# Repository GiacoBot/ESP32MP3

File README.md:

# **ESP32 MP3**

A self-built, portable MP3 player based on ESP32, combining a custom hardware design with an intuitive software interface. It reads music from an SD card, streams audio to any Bluetooth audio device, and is controlled via an OLED display and physical buttons.

## **Introduction**

This project evolved from a simple software experiment. The initial version was merely a proof-of-concept for Bluetooth audio streaming from an ESP32. Driven by the desire to create a complete and presentable product, I designed and built a custom dev board, developing an entire graphical and physical user interface from scratch.

The result is a functional and integrated device, demonstrating expertise in both hardware design (PCB design with KiCad) and complex firmware development (modular C++ architecture).

## **✨ Key Features**

#### **Hardware**

*   **Custom Dev Board (Rev 1.1)**: Development board entirely designed with KiCad to house all components compactly and functionally.
*   **0.96" OLED Display**: Monochrome screen (SSD1306 128x64) for a clear, low-power user interface.
*   **Physical Controls**: Interface navigation is managed by 5 physical buttons (Up, Down, Left, Right, Enter).
*   **MicroSD Card Storage**: A MicroSD card slot allows easy loading and playback of your music library.
*   **Power Management**: Power circuit with support for Li-Ion batteries and USB-C charging.

#### **Software**

*   **Bluetooth Audio Streaming (A2DP Source)**: Connects to Bluetooth headphones and speakers for high-quality wireless playback.
*   **Multi-screen User Interface**:
    *   **Bluetooth Device Selection**: Scans for nearby audio devices and manages the connection.
    *   **Track Selection**: Allows browsing the complete playlist of songs on the SD Card.
    *   **Now Playing**: Displays track information (if available), song title, artist, and a progress bar.
    *   **Volume Control**: Adjusts the playback volume directly from the interface.
*   **Advanced Playlist Management**: Automatically scans the SD card on startup to find all `.mp3` files.
*   **Intuitive User Input**: Supports short press, long press, and auto-repeat of buttons for smooth and fast navigation.
*   **Modular Firmware Architecture**: The code is organized into specialized "Managers" (Display, Input, Bluetooth, Player), making the system scalable, maintainable, and easy to debug.

## **⚙️ Hardware Details**

The development board was designed in KiCad to integrate the ESP32 with all necessary modules. The design is optimized for manual assembly and for use as a portable device.

*   **Design Software**: KiCad
*   **Main Processor**: ESP32-WROOM-32E module
*   **Display**: 0.96 inch (128x64) SSD1306 I2C/SPI OLED module
*   **Storage**: Standard MicroSD card reader
*   **Hardware Repository**: KiCad project files (schematics, PCB, and libraries) are available in the [`/Hardware/devboard Rev1.1`](/Hardware/devboard%20Rev1.1/) folder.

## **💻 Software Details**

The firmware is developed using the Arduino framework within PlatformIO, which simplifies dependency management and compilation.

*   **Framework**: Arduino / PlatformIO
*   **Key Libraries**:
    *   **[`U8g2`](https://github.com/olikraus/U8g2)**: Excellent library for managing monochrome displays.
    *   **[`arduino-audio-tools`](https://github.com/pschatzmann/arduino-audio-tools)**: For the audio decoding and processing pipeline.
    *   **[`ESP32-A2DP`](https://github.com/pschatzmann/ESP32-A2DP)**: For implementing the Bluetooth A2DP Source stack.
    *   **[`arduino-libhelix`](https://github.com/pschatzmann/arduino-libhelix)**: Provides the MP3 decoder based on Helix.
*   **Architecture**: The heart of the software is a state machine that manages navigation between different screens (`AppScreen`). The logic is divided into independent manager classes that communicate via an event system (`InputEvent`) and shared states, ensuring high cohesion and low coupling between modules.

## **🚀 Getting Started**

> [!NOTE]  
> If you want to try a simplified version of the project, you can try the alpha version, a proof of concept that only requires a breakout module for the micro SD and an ESP32 board. Follow the `README` in the alpha version for instructions.

#### **1. Hardware Prerequisites**

*   The assembled Dev Board.
*   A MicroSD card formatted as FAT32 and loaded with `.mp3` files. Is required for the files to have a sample rate of 44100 Hz, use the following `ffmpeg` command to convert files if needed:

    ```bash
    ffmpeg -i input.mp3 -ar 44100 output.mp3
    ```
*   A USB-C cable to upload the firmware.

#### **2. Software Setup**

The project is designed to be compiled with PlatformIO in Visual Studio Code.

1.  **Install VS Code and PlatformIO**: Follow the [official PlatformIO guide](https://platformio.org/install/ide?install=vscode).
2.  **Clone the Repository**:
    ```bash
    git clone https://github.com/GiacoBot/ESP32MP3.git
    cd ESP32MP3
    ```
3.  **Initialize Submodules**: The audio libraries are included as Git submodules.
    ```bash
    git submodule update --init --recursive
    ```

#### **3. Compile and Upload**

1.  **Open the Project**: In VS Code, open the project folder. Make sure to open the `Software` subfolder.
> [!IMPORTANT]  
> The PlatformIO project is located within the `Software` folder. When you open this project in VS Code, make sure you open the `Software` directory, not the root of the repository, to ensure PlatformIO can find all the necessary files.

1.  **Change Board settings**: Modify the `src/settings.h` file to match your hardware configuration if necessary (e.g., pin assignments).
2.  **Compile and Upload**: Use the PlatformIO commands (down arrow on the status bar) to build and upload the firmware to the board.

## **📸 Gallery**

Various screenshots of the user interface:

## **📜 License**

This project is released under the GPL-3.0 License. See the [LICENSE](LICENSE) file for more details.

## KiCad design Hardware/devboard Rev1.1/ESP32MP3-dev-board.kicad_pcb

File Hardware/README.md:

# Hardware

This folder contains the hardware design files for the project's custom development board.
Each hardware revision is organized in its own subfolder to keep designs clean, traceable, and easy to reference.

### Dev boards

* **Devboard Rev1.0** – First prototype of the dev board. Includes schematics, PCB layout, Gerber files, and BOM.
* **Devboard Rev1.1** – Updated revision addressing small issues found in Rev1.0. Recommended for new builds.

The development board is a semi-finished prototype, created to also validate the electrical design of the battery-charging circuitry and the buck-boost voltage regulation stage.
Its purpose is to verify the power system and provide a convenient and compact development board.

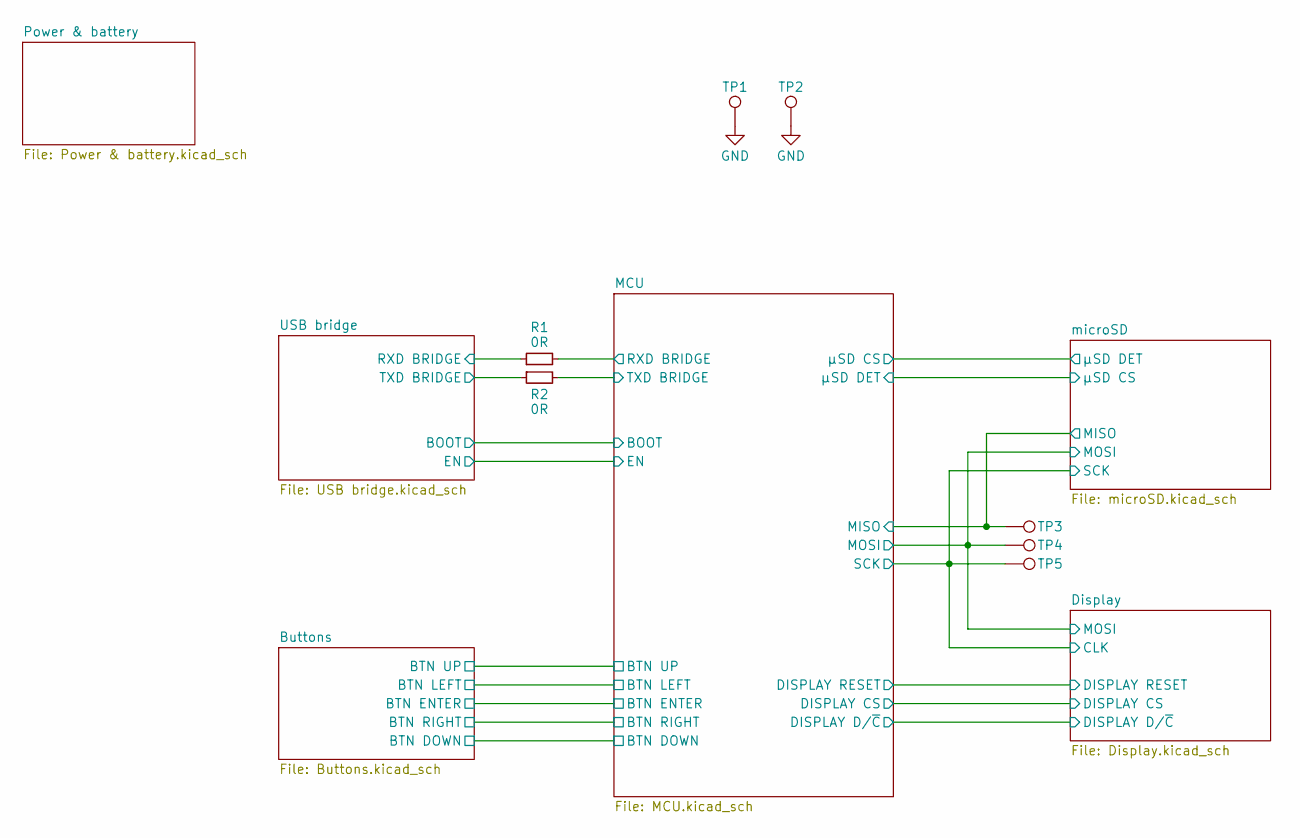
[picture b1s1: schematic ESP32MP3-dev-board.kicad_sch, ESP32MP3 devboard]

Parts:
R1, R2: 0R; R_0603_1608Metric_Pad0.98x0.95mm_HandSolder; Part Number YAGEO RC0603JR-070RL
TP1, TP2: GND; TestPoint_Pad_1.0x1.0mm
TP3: MISO; TestPoint_Pad_D1.0mm
TP4: MOSI; TestPoint_Pad_D1.0mm
TP5: SCK; TestPoint_Pad_D1.0mm

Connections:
/Display/CLK: TP5.1; also elsewhere on the board
/Display/MOSI: TP4.1; also elsewhere on the board
/MCU/MISO: TP3.1; also elsewhere on the board
/MCU/RXD BRIDGE: R1.2; also elsewhere on the board
/MCU/TXD BRIDGE: R2.2; also elsewhere on the board
/USB bridge/RXD BRIDGE: R1.1; also elsewhere on the board
/USB bridge/TXD BRIDGE: R2.1; also elsewhere on the board
GND: TP1.1, TP2.1; also elsewhere on the board

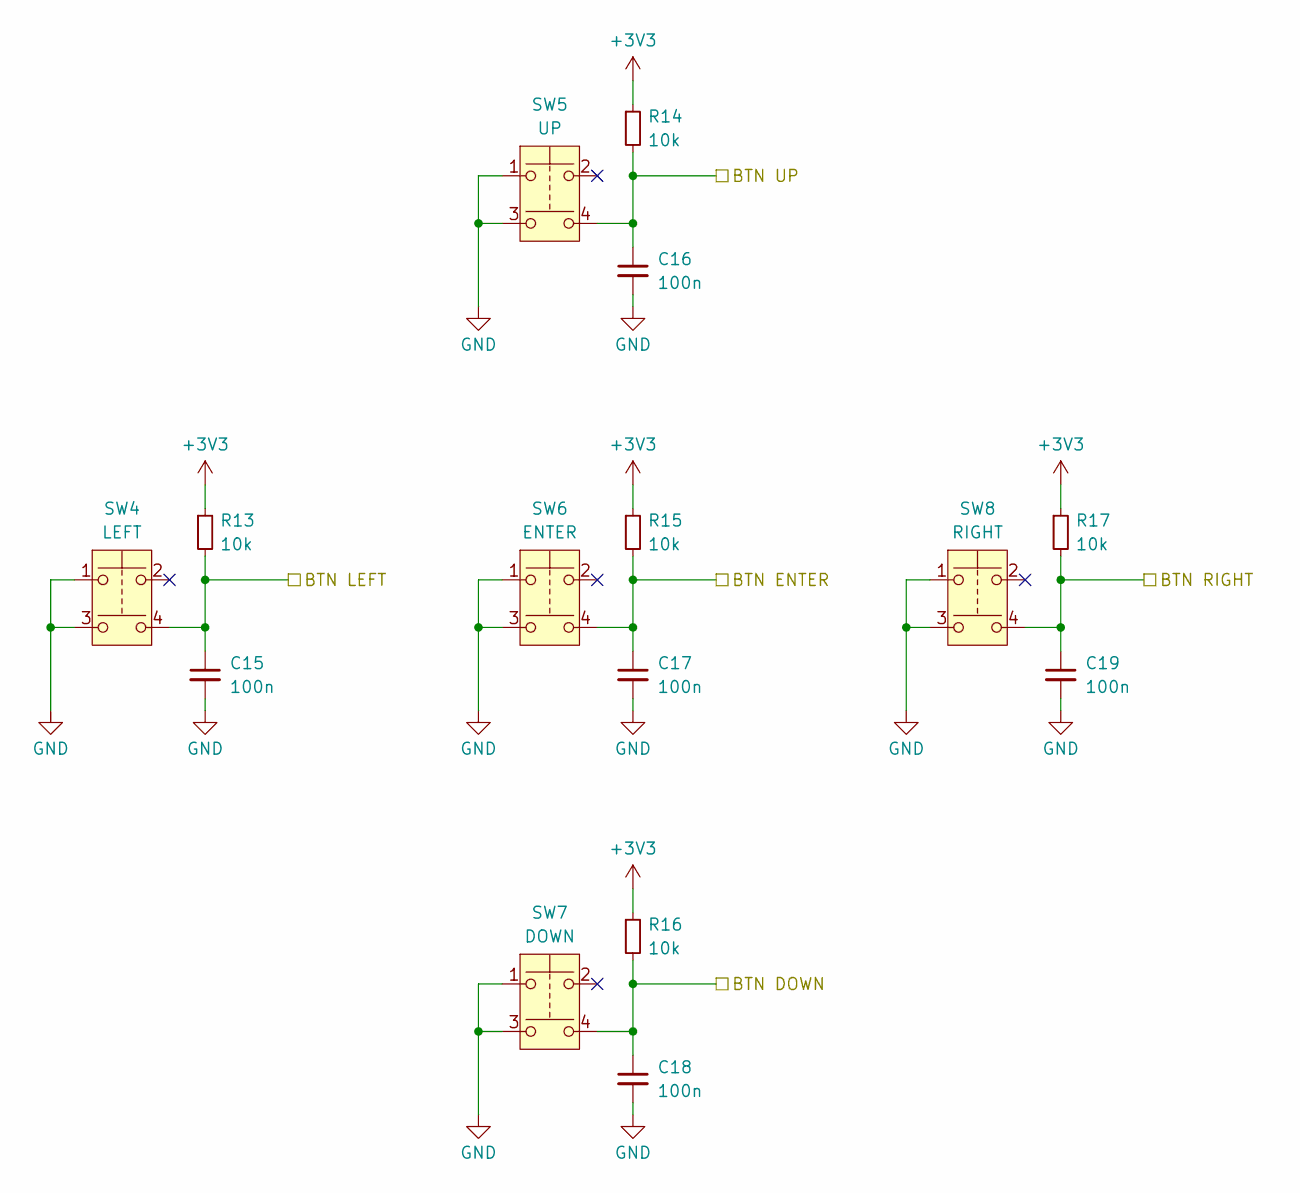
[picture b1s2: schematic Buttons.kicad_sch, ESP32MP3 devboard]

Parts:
C15, C16, C17, C18, C19: 100n; C_0603_1608Metric; Part Number YAGEO CC0603KRX7R9BB104
R13, R14, R15, R16, R17: 10k; R_0603_1608Metric_Pad0.98x0.95mm_HandSolder; Part Number YAGEO RC0603FR-0710KL
SW4: LEFT; PTS526SM15SMTR2LFS; Part Number C&K PTS526SK15SMTR2LFS
SW5: UP; PTS526SM15SMTR2LFS; Part Number C&K PTS526SK15SMTR2LFS
SW6: ENTER; PTS526SM15SMTR2LFS; Part Number C&K PTS526SK15SMTR2LFS
SW7: DOWN; PTS526SM15SMTR2LFS; Part Number C&K PTS526SK15SMTR2LFS
SW8: RIGHT; PTS526SM15SMTR2LFS; Part Number C&K PTS526SK15SMTR2LFS

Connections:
+3V3: R13.1, R14.1, R15.1, R16.1, R17.1; also elsewhere on the board
/Buttons/BTN DOWN: C18.1, R16.2, SW7.4; also elsewhere on the board
/Buttons/BTN ENTER: C17.1, R15.2, SW6.4; also elsewhere on the board
/Buttons/BTN LEFT: C15.1, R13.2, SW4.4; also elsewhere on the board
/Buttons/BTN RIGHT: C19.1, R17.2, SW8.4; also elsewhere on the board
/Buttons/BTN UP: C16.1, R14.2, SW5.4; also elsewhere on the board
GND: C15.2, C16.2, C17.2, C18.2, C19.2, SW4.1, SW4.3, SW5.1, SW5.3, SW6.1, SW6.3, SW7.1, SW7.3, SW8.1, SW8.3; also elsewhere on the board

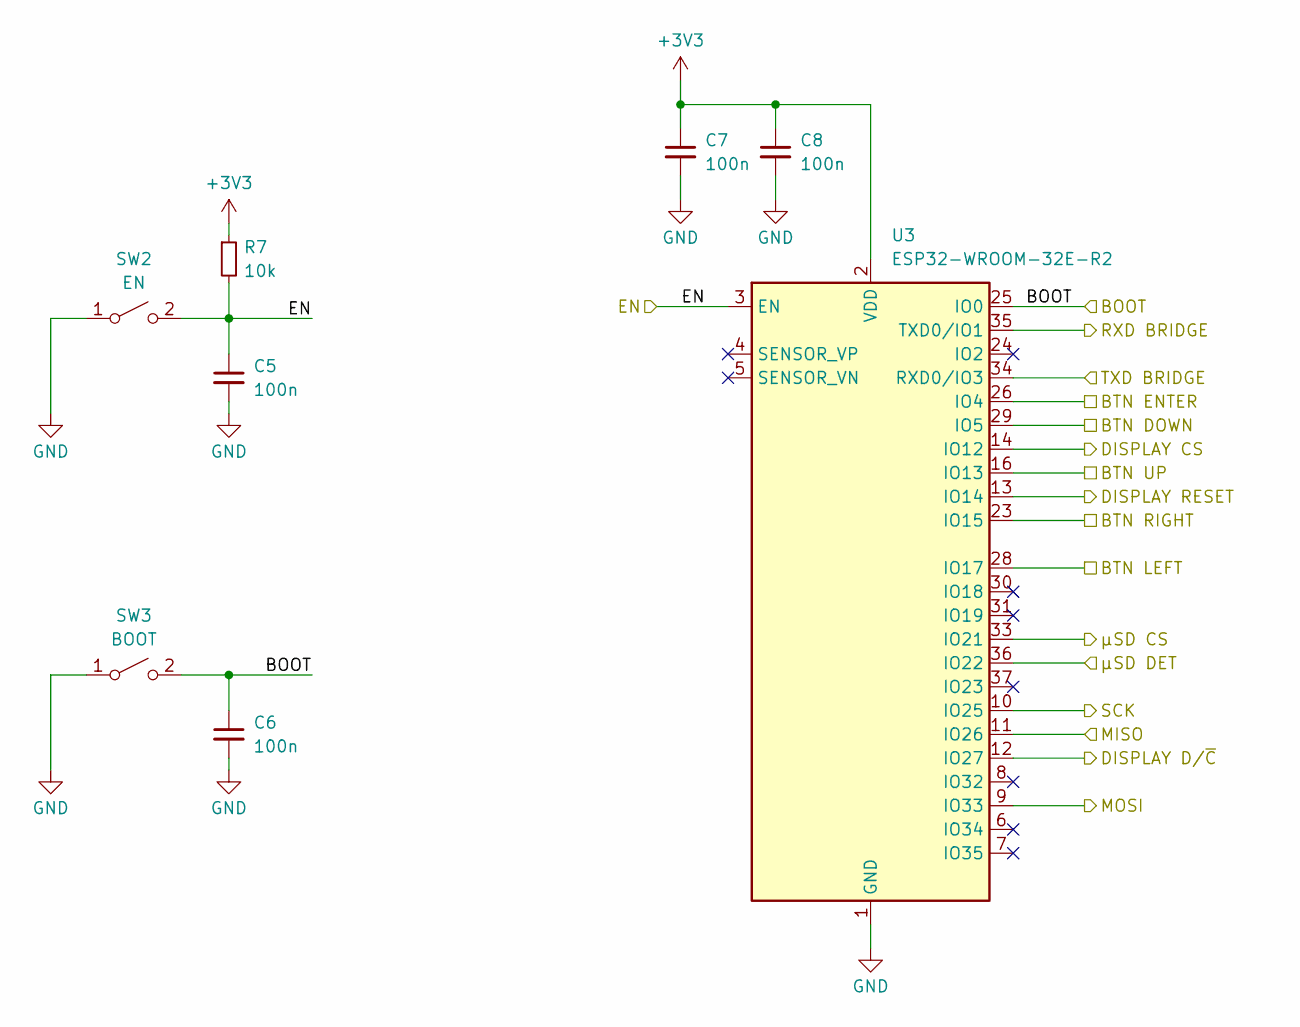
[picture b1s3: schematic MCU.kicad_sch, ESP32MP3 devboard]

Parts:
C5, C6, C7, C8: 100n; C_0603_1608Metric; Part Number YAGEO CC0603KRX7R9BB104
R7: 10k; R_0603_1608Metric_Pad0.98x0.95mm_HandSolder; Part Number YAGEO RC0603FR-0710KL
SW2: EN; SW_TS-1088-AR02016; Part Number XUNPU TS-1088-AR02016
SW3: BOOT; SW_TS-1088-AR02016; Part Number XUNPU TS-1088-AR02016
U3: ESP32-WROOM-32E-R2; ESP32-WROOM-32D; Part Number ESPRESSIF ESP32-WROOM-32E-N8R2

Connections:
+3V3: C7.1, C8.1, R7.1, U3.2 (VDD); also elsewhere on the board
/Buttons/BTN DOWN: U3.29 (IO5); also elsewhere on the board
/Buttons/BTN ENTER: U3.26 (IO4); also elsewhere on the board
/Buttons/BTN LEFT: U3.28 (IO17); also elsewhere on the board
/Buttons/BTN RIGHT: U3.23 (IO15); also elsewhere on the board
/Buttons/BTN UP: U3.16 (IO13); also elsewhere on the board
/Display/CLK: U3.10 (IO25); also elsewhere on the board
/Display/DISPLAY CS: U3.14 (IO12); also elsewhere on the board
/Display/DISPLAY D/~C: U3.12 (IO27); also elsewhere on the board
/Display/DISPLAY RESET: U3.13 (IO14); also elsewhere on the board
/Display/MOSI: U3.9 (IO33); also elsewhere on the board
/MCU/BOOT: C6.1, SW3.2 (B), U3.25 (IO0); also elsewhere on the board
/MCU/EN: C5.1, R7.2, SW2.2 (B), U3.3 (EN); also elsewhere on the board
/MCU/MISO: U3.11 (IO26); also elsewhere on the board
/MCU/RXD BRIDGE: U3.35 (TXD0/IO1); also elsewhere on the board
/MCU/TXD BRIDGE: U3.34 (RXD0/IO3); also elsewhere on the board
/MCU/µSD CS: U3.33 (IO21); also elsewhere on the board
/MCU/µSD DET: U3.36 (IO22); also elsewhere on the board
GND: C5.2, C6.2, C7.2, C8.2, SW2.1 (A), SW3.1 (A), U3.1 (GND), U3.15 (GND), U3.38 (GND), U3.39 (GND); also elsewhere on the board

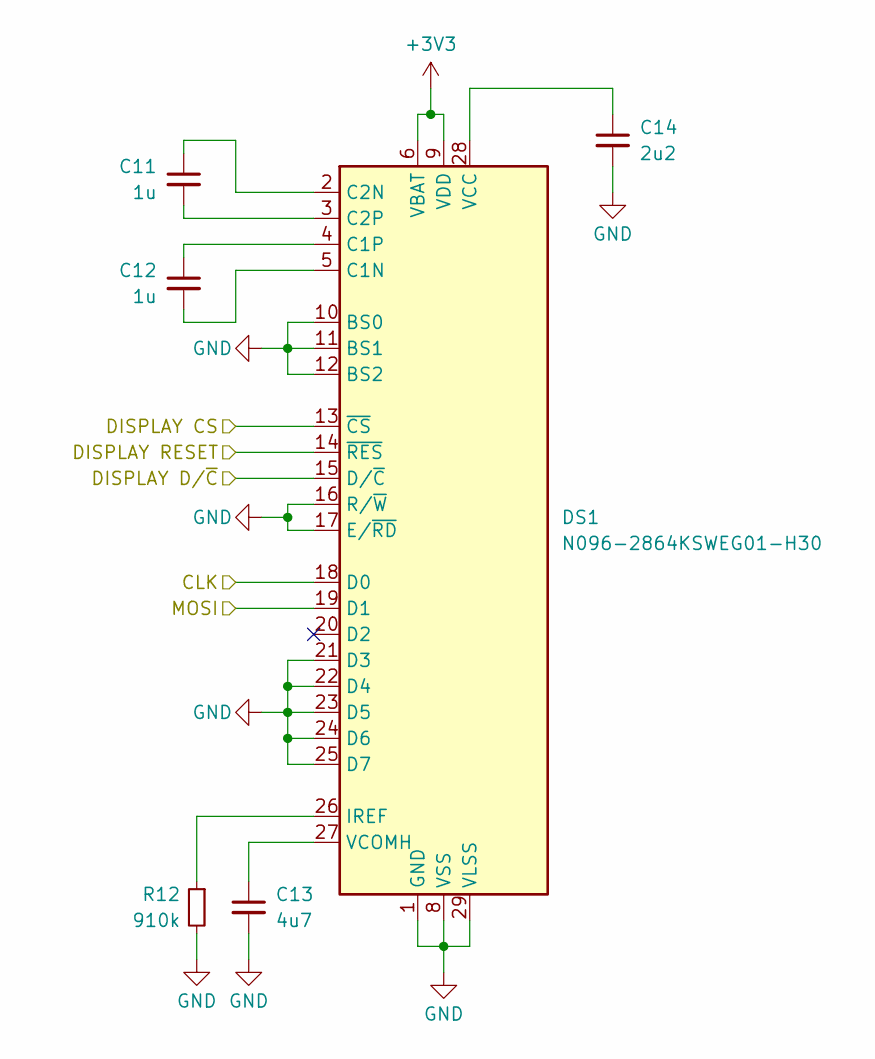
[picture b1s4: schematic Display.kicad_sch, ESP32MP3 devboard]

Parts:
C11, C12: 1u; C_0603_1608Metric; Part Number Samsung Electro-Mechanics CL10B105KA8NN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
C13: 4u7; C_0603_1608Metric; Part Number Samsung Electro-Mechanics CL10A475KA8NQ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
C14: 2u2; C_0603_1608Metric; Part Number muRata GRM188Z71E225KE43D
DS1: N096-2864KSWEG01-H30; Part Number Wisevision N096-2864KSWEG01-H30
R12: 910k; R_0603_1608Metric_Pad0.98x0.95mm_HandSolder; Part Number YAGEO RC0603FR-07910KL

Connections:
+3V3: DS1.6 (VBAT), DS1.9 (VDD); also elsewhere on the board
/Display/CLK: DS1.18 (D0); also elsewhere on the board
/Display/DISPLAY CS: DS1.13 (~CS); also elsewhere on the board
/Display/DISPLAY D/~C: DS1.15 (D/~C); also elsewhere on the board
/Display/DISPLAY RESET: DS1.14 (~RES); also elsewhere on the board
/Display/MOSI: DS1.19 (D1); also elsewhere on the board
GND: C13.2, C14.2, DS1.1 (GND), DS1.8 (VSS), DS1.10 (BS0), DS1.11 (BS1), DS1.12 (BS2), DS1.16 (R/~W), DS1.17 (E/~RD), DS1.21 (D3), DS1.22 (D4), DS1.23 (D5), DS1.24 (D6), DS1.25 (D7), DS1.29 (VLSS), DS1.30 (GND), R12.2; also elsewhere on the board
unnamed: C12.2, DS1.5 (C1N)
unnamed: C12.1, DS1.4 (C1P)
unnamed: C11.1, DS1.2 (C2N)
unnamed: C11.2, DS1.3 (C2P)
unnamed: DS1.26 (IREF), R12.1
unnamed: C14.1, DS1.28 (VCC)
unnamed: C13.1, DS1.27 (VCOMH)

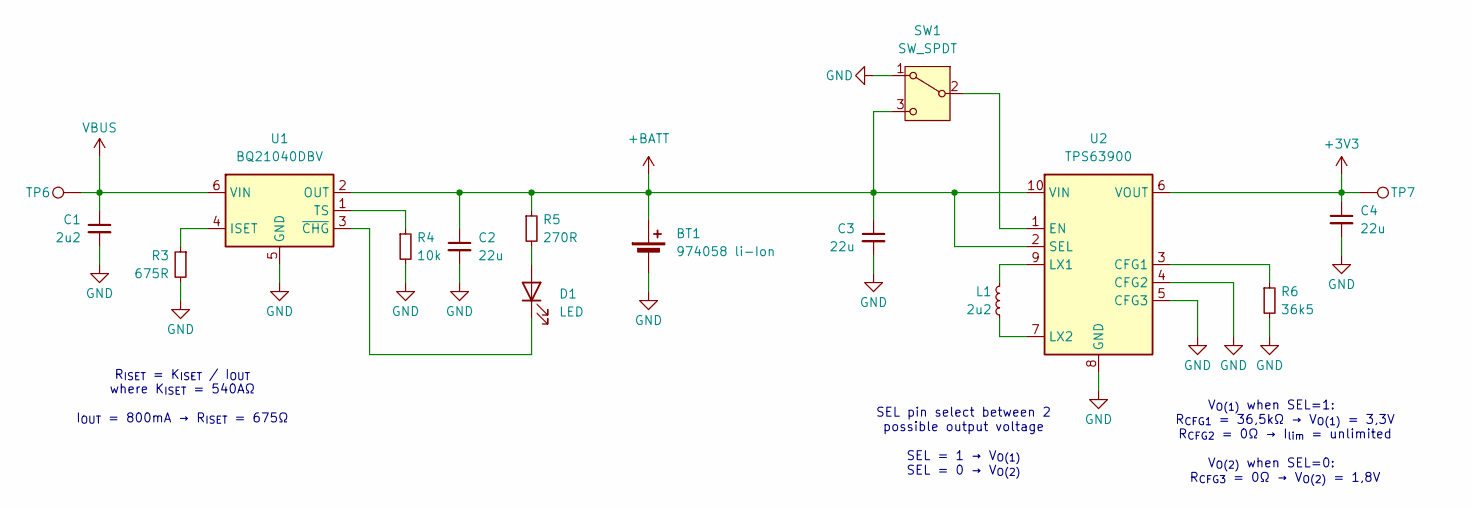
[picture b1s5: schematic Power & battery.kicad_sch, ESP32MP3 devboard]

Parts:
BT1: 974058 li-Ion; JST_PH_S2B-PH-SM4-TB_1x02-1MP_P2.00mm_Horizontal; Part Number JST S2B-PH-SM4-TB(LF)(SN)
C1: 2u2; C_0603_1608Metric; Part Number muRata GRM188Z71E225KE43D
C2, C3, C4: 22u; C_0603_1608Metric; Part Number Samsung Electro-Mechanics CL10A226MP8NU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
D1: LED; LED_0603_1608Metric; Part Number EVERLIGHT 19-219/GHC-YR2T1B5Y/3T
L1: 2u2; L_1008_2520Metric; Part Number ZE ZEMS252012-2R2M
R3: 675R; R_0603_1608Metric_Pad0.98x0.95mm_HandSolder; Part Number YAGEO RC0603FR-07680RL
R4: 10k; R_0603_1608Metric_Pad0.98x0.95mm_HandSolder; Part Number YAGEO RC0603FR-0710KL
R5: 270R; R_0603_1608Metric_Pad0.98x0.95mm_HandSolder; Part Number YAGEO RC0603FR-07270RL
R6: 36k5; R_0603_1608Metric_Pad0.98x0.95mm_HandSolder; Part Number YAGEO RT0603BRE0736K5L
SW1: SW_SPDT; MK-12C02-G015; Part Number G-Switch MK-12C02-G015
TP6: 5V; TestPoint_Pad_D1.0mm
TP7: 3V3; TestPoint_Pad_D1.0mm
U1: BQ21040DBV; SOT-23-6; Part Number TI BQ21040DBVR
U2: TPS63900; WSON-10-1EP_2.5x2.5mm_P0.5mm_EP1.2x2mm_ThermalVias; Part Number TI TPS63900DSKR

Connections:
+3V3: C4.1, TP7.1, U2.6 (VOUT); also elsewhere on the board
+BATT: BT1.2 (+), C2.1, C3.1, R5.1, SW1.3 (C), U1.2 (OUT), U2.2 (SEL), U2.10 (VIN)
GND: BT1.1 (-), C1.2, C2.2, C3.2, C4.2, R3.2, R4.2, R6.2, SW1.1 (A), U1.5 (GND), U2.4 (CFG2), U2.5 (CFG3), U2.8 (GND), U2.11 (GND); also elsewhere on the board
unnamed: D1.2 (A), R5.2
unnamed: D1.1 (K), U1.3 (~CHG)
unnamed: SW1.2 (B), U2.1 (EN)
unnamed: R3.1, U1.4 (ISET)
unnamed: R4.1, U1.1 (TS)
unnamed: R6.1, U2.3 (CFG1)
unnamed: L1.1, U2.9 (LX1)
unnamed: L1.2, U2.7 (LX2)
VBUS: C1.1, TP6.1, U1.6 (VIN); also elsewhere on the board

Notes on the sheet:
R_{ISET} = K_{ISET} / I_{OUT} where K_{ISET} = 540AΩ I_{OUT} = 800mA → R_{ISET} = 675Ω
SEL pin select between 2 possible output voltage SEL = 1 → V_{O(1)} SEL = 0 → V_{O(2)}
V_{O(1)} when SEL=1: R_{CFG1} = 36,5kΩ → V_{O(1)} = 3,3V R_{CFG2} = 0Ω → I_{lim} = unlimited V_{O(2)} when SEL=0: R_{CFG3} = 0Ω → V_{O(2)} = 1,8V

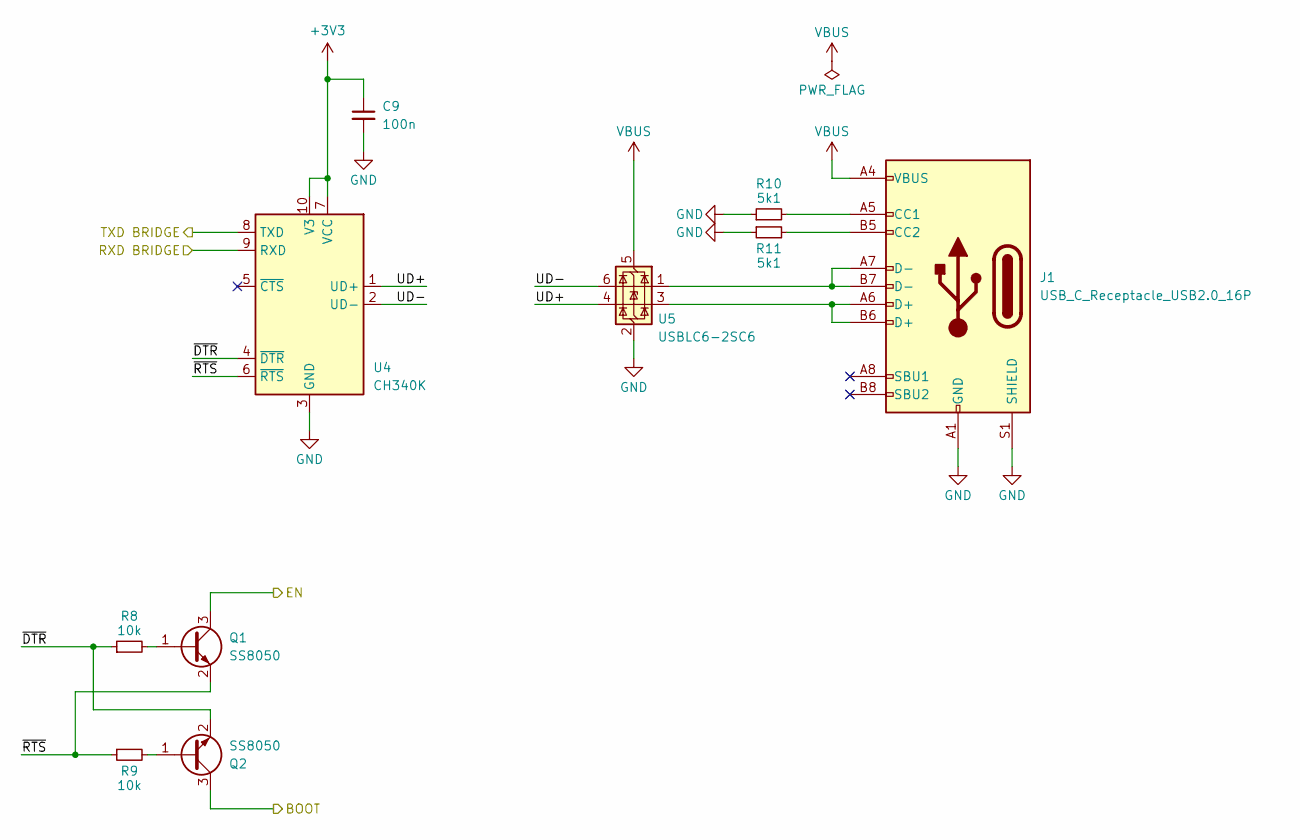
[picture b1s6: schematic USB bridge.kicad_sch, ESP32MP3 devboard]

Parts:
C9: 100n; C_0603_1608Metric; Part Number YAGEO CC0603KRX7R9BB104
J1: USB_C_Receptacle_USB2.0_16P; USB_C_Receptacle_GCT_USB4110; Part Number DEALON USB-TYPE-C-020
Q1, Q2: SS8050; SOT-23-3; Part Number Chao He SS8050
R8, R9: 10k; R_0603_1608Metric_Pad0.98x0.95mm_HandSolder; Part Number YAGEO RC0603FR-0710KL
R10, R11: 5k1; R_0603_1608Metric_Pad0.98x0.95mm_HandSolder; Part Number YAGEO RC0603FR-075K1L
U4: CH340K; SSOP-10-1EP_3.9x4.9mm_P1mm_EP2.1x3.3mm; Part Number WCH CH340K
U5: USBLC6-2SC6; SOT-23-6; Part Number TECH PUBLIC USBLC6-2SC6

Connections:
+3V3: C9.1, U4.7 (VCC), U4.10 (V3); also elsewhere on the board
/MCU/BOOT: Q2.3 (C); also elsewhere on the board
/MCU/EN: Q1.3 (C); also elsewhere on the board
/USB bridge/RXD BRIDGE: U4.9 (RXD); also elsewhere on the board
/USB bridge/TXD BRIDGE: U4.8 (TXD); also elsewhere on the board
/USB bridge/UD+: U4.1 (UD+), U5.4 (I/O2)
/USB bridge/UD-: U4.2 (UD-), U5.6 (I/O1)
/USB bridge/~DTR: Q2.2 (E), R8.1, U4.4 (~DTR)
/USB bridge/~RTS: Q1.2 (E), R9.1, U4.6 (~RTS)
GND: C9.2, J1.A1 (GND), J1.A12 (GND), J1.B1 (GND), J1.B12 (GND), J1.S1 (SHIELD), R10.1, R11.1, U4.3 (GND), U4.11 (GND), U5.2 (GND); also elsewhere on the board
unnamed: J1.A5 (CC1), R10.2
unnamed: J1.B5 (CC2), R11.2
unnamed: J1.A6 (D+), J1.B6 (D+), U5.3 (I/O2)
unnamed: J1.A7 (D-), J1.B7 (D-), U5.1 (I/O1)
unnamed: Q1.1 (B), R8.2
unnamed: Q2.1 (B), R9.2
VBUS: J1.A4 (VBUS), J1.A9 (VBUS), J1.B4 (VBUS), J1.B9 (VBUS), U5.5 (VBUS); also elsewhere on the board

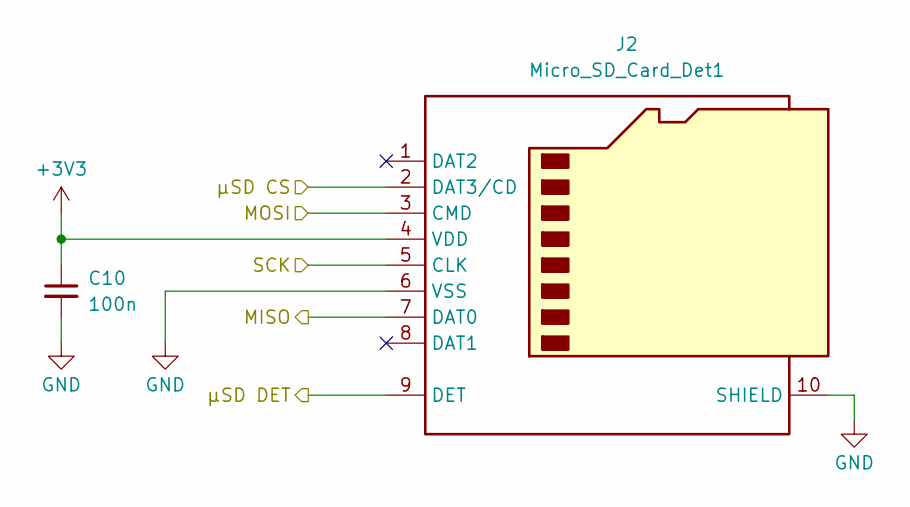
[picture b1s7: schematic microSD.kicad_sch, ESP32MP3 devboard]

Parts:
C10: 100n; C_0603_1608Metric; Part Number YAGEO CC0603KRX7R9BB104
J2: Micro_SD_Card_Det1; TF PUSH; Part Number SHOU HAN TF PUSH

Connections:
+3V3: C10.1, J2.4 (VDD); also elsewhere on the board
/Display/CLK: J2.5 (CLK); also elsewhere on the board
/Display/MOSI: J2.3 (CMD); also elsewhere on the board
/MCU/MISO: J2.7 (DAT0); also elsewhere on the board
/MCU/µSD CS: J2.9 (DET); also elsewhere on the board
/MCU/µSD DET: J2.2 (DAT3/CD); also elsewhere on the board
GND: C10.2, J2.6 (VSS), J2.10 (SHIELD); also elsewhere on the board

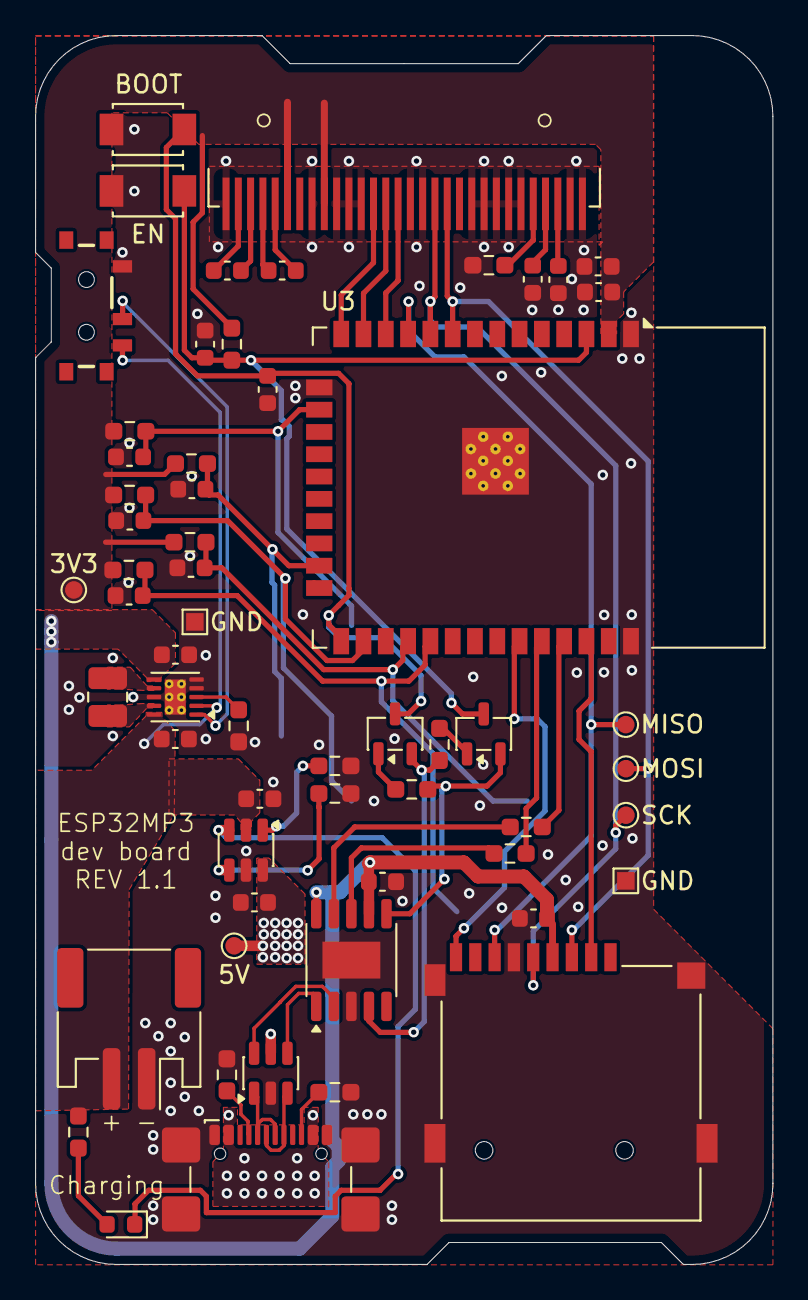
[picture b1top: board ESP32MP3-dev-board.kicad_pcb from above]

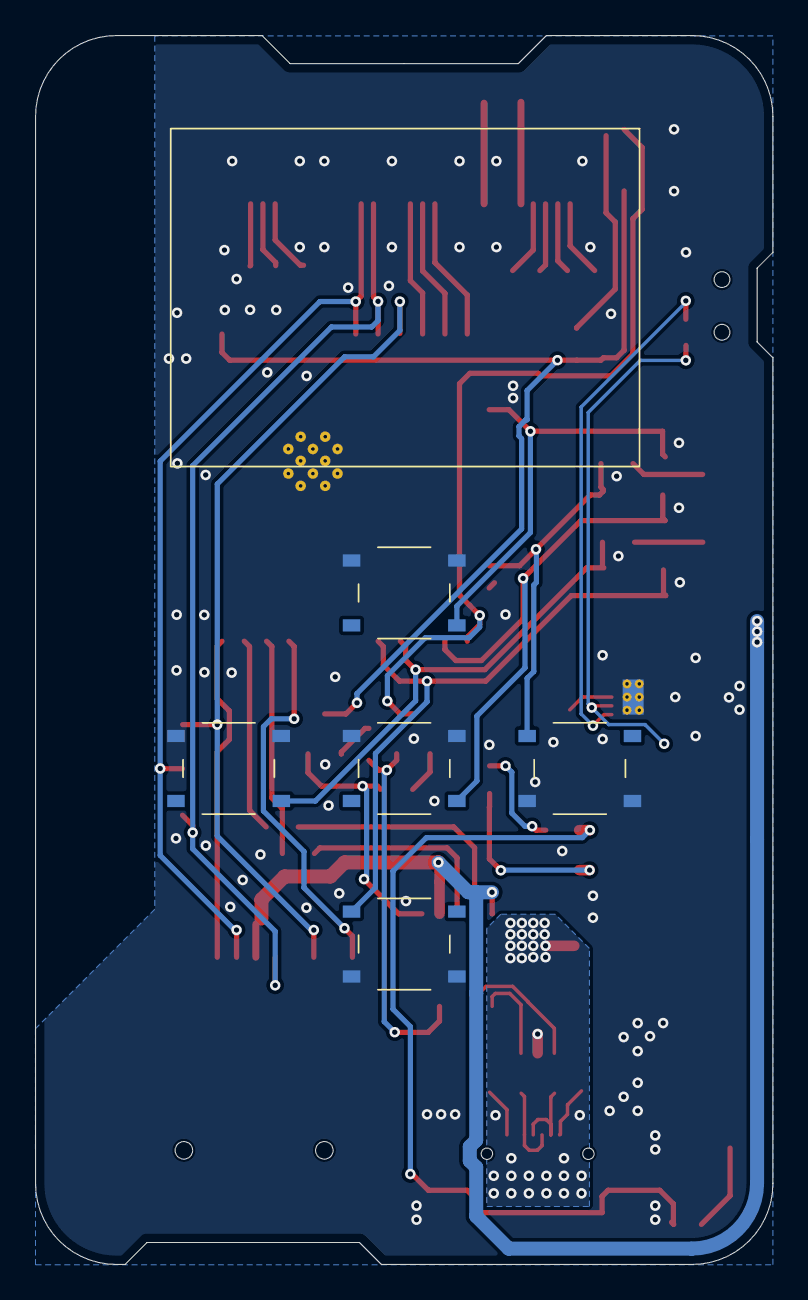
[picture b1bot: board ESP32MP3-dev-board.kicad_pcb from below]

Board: 2 copper layers, 42.0 x 70.0 mm, 64 parts (5 on the bottom side), 48 nets.

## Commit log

2025-08-13 add Bluetooth MP3 player functionality with playlist management and A2DP support
2025-08-13 add Hardware folder
2025-08-14 modularized code by splitting file into sub-files
2025-12-01 PoC of buttons and OLED display
2025-12-01 modularized buttons and display code
2025-12-01 improved infos on display
2025-12-01 improved SPI initialization
2025-12-02 moved settings into settings.h
2025-12-02 added splash screen
2025-12-03 switched to U8g2 library for the display
2025-12-03 added menus to interface WIP
2025-12-05 improved scrolling logic on list menus
2025-12-05 added scrolling text to long menu list entries
2025-12-06 added scroll bar on long lists
2025-12-06 fixed scrolling text hide under scroll bar
2025-12-06 improved input management with long and repeated button press
2025-12-06 improved bluetooth menu
2025-12-06 added connecting screen to bluetooth
2025-12-06 switch to using buttons in U8g2
2025-12-06 added automatic switch to NOW_PLAYING menu when connected
2025-12-07 updated libraries
2025-12-08 added project of devboard rev1.0
2025-12-08 added project of devboard Rev1.1
2025-12-08 fixed switch footprint and changed buttons pins to avoid bootstrapping pins
2025-12-08 updated readme for hardware section
2025-12-09 suca giacomo
2025-12-10 suca giacomo 2
2025-12-10 removed serial controller
2025-12-12 Disable watchdog timer to avoid reboots from MP3 Metadata
    My ESP32 board reboots continually when I put music with some Metadata.
    This works and keeps playing the music, but it would probably be better to apply the filter explained by the Helix library author:
    https://github.com/pschatzmann/arduino-audio-tools/wiki/Audio-Metadata#metadata-and-decoders
    (I don't know how to do that) :-)
2026-01-21 Refactor image tags in README
2026-01-27 added volume control management and UI
2026-01-27 added playlist index file to preserve RAM
2026-01-27 added cache to track name to improve performance
2026-01-28 optimized index file for improve heap usage
2026-01-28 splitted playlist file for faster access
2026-01-28 fixed stopDiscovery
2026-01-28 removed redundant call added to the library
2026-01-31 improved NOW_PLAYING interface
